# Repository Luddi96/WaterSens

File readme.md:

Universaler Zisternen-Füllstandsmesser

Einleitung:

Jeder Besitzer einer Regenzisterne kennt diese Frage: Wie viel Wasser verbleibt mir noch und wie viel hat der letzte Regen wieder aufgefüllt? Um Abhilfe zu schaffen gibt es eine Reihe an Messgeräten und Sensoren: Ganz simpel mit mehren Elektroden auf verschiedenen Höhen, kapazitiv unter Zuhilfenahme der Dielektrizitätskonstante des Wassers selbst, per Ultraschall oder per Druckmessung. Einige dieser Messungen haben Vorteile gegenüber anderen. In diesem Beitrag möchte ich Ihnen eine Methode zur Messung vorstellen, welche weder durch Temperatur, Luftdruck oder Leitfähigkeit des Wassers verfälscht wird und außerdem selbstreinigend (wartungsfrei) agiert. Die Messgenauigkeit liegt bei umgerechnet 20 Liter in einer 7500 Liter Zisterne, also etwa 0,3%!
Das Projekt involviert die Programmierung eines ATMega Mikrocontrollers, das Löten von SMD Bauteilen (es könnte aber auch als THT aufgebaut werden) sowie grundlegende mechanische Fähigkeiten.
Das Funktionsprinzip:
Wie funktioniert der Sensor? Im Prinzip ganz einfach: Man misst den Druck, den das Wasser an der tiefsten Stelle der Zisterne erzeugt. Dieser ist proportional zur Höhe des Wassers und somit (bei einer gleichförmigen Zisterne) ebenfalls proportional zum Füllstand. Würde man aber einfach einen Sensor auf den Grund der Zisterne herablassen, so stößt man auf 3 Probleme: 1. Solche Sensoren sind recht teuer (müssen ja auch wasserdicht sein) 2. Es gibt keine Möglichkeit, den Sensor periodisch zu nullen 3. Der Luftdruck beeinflusst das Ergebnis: 10hPa Druckunterschied bedeuten bereits 100mm Wassersäule oder einen Messfehler von etwa 750 Liter in bzw. 10% in einer 7500 Liter Zisterne.
Mit einem Trick können aber alle der eben genannten Einflüsse kompensiert werden: In die Zisterne wird lediglich ein dünner Schlauch mit einem Gewicht am offenen Ende eingeführt und bis zum Boden herabgelassen. In das andere Ende wird mit einer kleinen Luftpumpe so lange Luft gepumpt, bis dieser komplett gefüllt ist und erste Luftblasen austreten. Der Druck im Schlauch entspricht dann genau dem Druck am Boden der Zisterne. Mit einem empfindlichen Drucksensor kann dieser dann ausgelesen werden. Wenn der Schlauch vor und nach der Messung mittels einem Magnetventil entleert wird, können Umgebungsdruck und Langzeit-Drift des Drucksensor eliminiert werden. Ebenso ist das System durch das "Ausspülen" des Schlauches bei jeder Messung selbstreinigend.

Komponenten:

1x Miniatur-Luftpumpe JQB031 oder ähnlich https://bit.ly/2ENsoDM
2x 3-Wege Magnetventil DQF2-6A-4 von dyxminipump https://bit.ly/2G6OzFo
1x Schlauch-Verbinder-Sortiment https://bit.ly/31LYU29
1x 50cm Silikonschlauch (2mm ID) https://bit.ly/2QGRM0I
1x 5m Silikonschlauch (4mm ID) https://bit.ly/34PzMJN
1x MPRLS Sensor-Modul https://www.adafruit.com/product/3965
1x Funkmodul, z.B. NRF24L01
1x Hauptleiterplatte, BOM als ZIP im Anhang
1x LiPo Einzelzelle 1000mAh https://bit.ly/2EHX8WZ

Aufbau:

Die Ansteuerung der Pumpe und Magnetventile sowie das Auslesen und Auswerten des Drucksensor und das anschließende Versenden der Daten per Funk übernimmt die Hauptleiterplatte. Auf dieser befindet sich ein ATMega328P-AU, geflasht mit dem Arudino Nano Bootloader. Zur Ansteuerung der Aktoren genügt ein IRF7103. Da der Sensor mehrere Jahre ohne Batteriewechsel auskommen soll, wird zur Spannungsversorgung ein TPS7A05 LDO mit einer Ausgangsspannung von 3,3V und einem Eigenstromverbrauch von nur 1uA verbaut. Auch der Spannungsteiler zur Messung der Batteriespannung wird über einen Optokoppler geschalten. So kommt das Gesamtsystem auf 6uA Sleep-Strom und bis zu 2 Jahre Lebensdauer bei 2 Messungen am Tag.
Die Pumpe sowie Magnetventile werden wie folgt verbunden:

Mit dem ersten Magnetventil kann der Druck aus dem System abgelassen werden, das andere Magnetventil schneidet "Messschlauch" und Drucksensor vom Rest ab, um einen Druckabfall während der Messung zu verhindern.
Das ganze wird auf einem 3D-Druck-Träger (.stl in der zip-Datei enthalten) in ein Modulgehäuse wasserdicht eingebaut. Der Druckausgleich wird mit einem Druckausgleichselement erreicht.
In der Software sieht der Ablauf wie folgt aus:
Initialisierung: Ports, Variablen, etc. initialisieren, Sensorwert auf 0 setzen
Start einer Messung:
-Druck im offenen System 3x messen, Wert als "before" speichern
-Magnetventil 1 schließen, Pumpe aktivieren
-Nach bestimmter Zeit Magnetventil 2 schließen, Pumpe abschalten und Magnetventil 1 wieder öffnen (der Schlauch steht jetzt unter Druck)
-Druck 3x messen, Wert als "high" speichern
-Magnetventil 2 öffnen und Druck entweichen lassen
-Druck 3x messen und als "after" speichern
-Aus before, after und high die Druckdifferenz berechnen, das ist das Ergebnis.
Eine solche Messung dauert etwa 8 Sekunden.
Fazit und Ergebnisse:
Ich habe das System nun schon seit 2 Monaten in Betrieb. Um die Haltbarkeit zu testen habe ich den Messintervall auf 60 Sekunden verringert und insgesamt hat das System bereits über 25.000 Messungen durchgeführt - ohne Probleme. Die Standardabweichung der Messung liegt bei etwa 2,5mm Wassersäule oder 20 Liter bei einer 7500 Liter Zisterne. Mir gefällt das System sehr gut. Ich habe bereits ein weiteres System gebaut, welches bei einem Bekannten eingebaut wird. Dort ersetzen wir das Funkmodul durch ein LAN-Modul, das System wird zudem dauerhaft mit Strom versorgt.

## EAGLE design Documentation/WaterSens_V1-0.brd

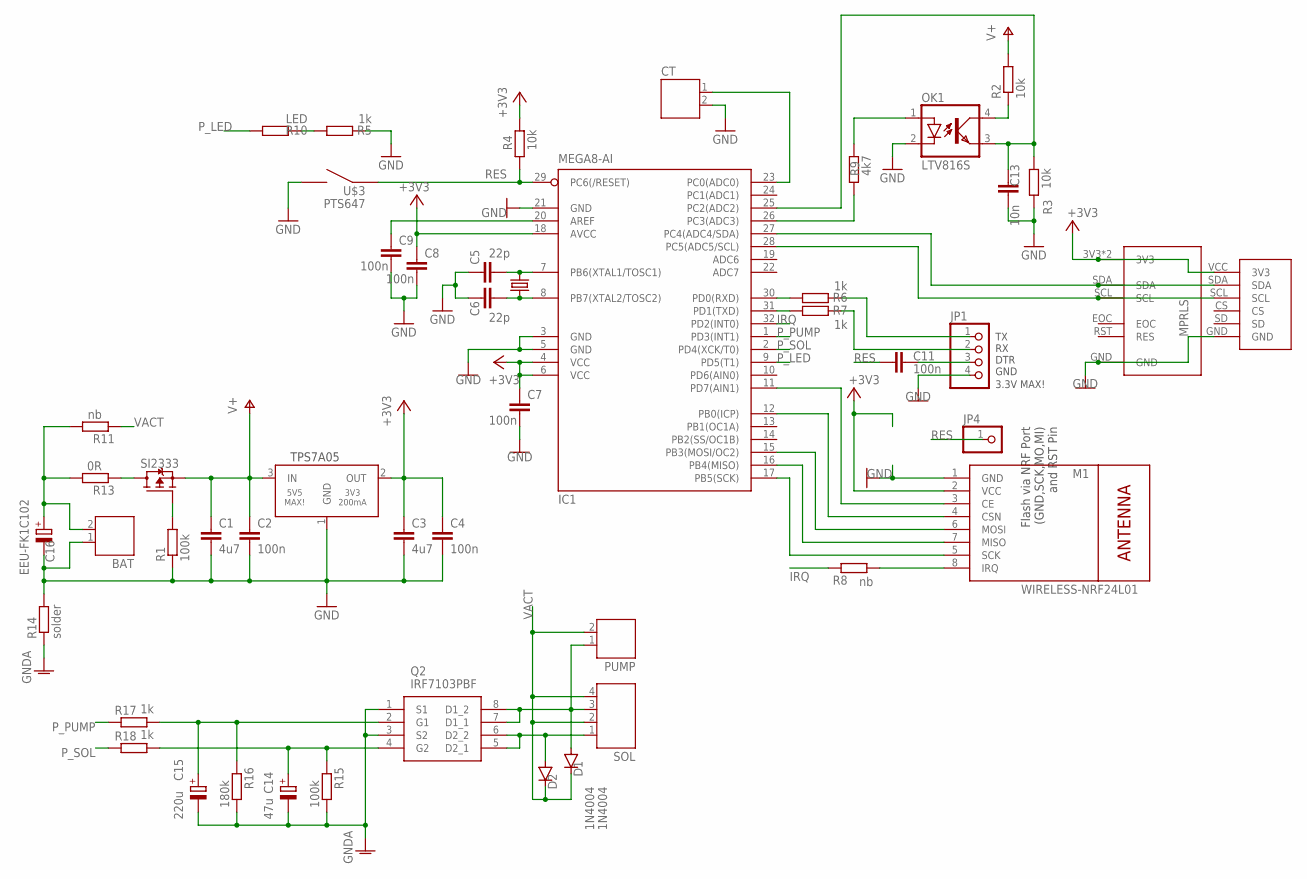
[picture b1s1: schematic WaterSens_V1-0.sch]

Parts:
BAT: JST-PH2
C1, C3: 4u7; C0805
C2, C4, C7, C8, C9, C11: 100n; C0805
C5, C6: 22p; C0805
C13: 10n; C0805
C14: 47u; E1,8-4
C15: 220u; E2,5-6E
C16: EEU-FK1C102; E5-10,5
CT: JST-PH2
D1, D2: 1N4004; DO41-10
IC1: MEGA8-AI; TQFP32-08
JP1: PINHD-1X4; 1X04
JP4: PINHD-1X1; 1X01
M1: WIRELESS-NRF24L01
OK1: LTV816S; DIL4-SMD
PUMP: JST-PH2
Q1: CRYSTALHC49UP; HC49UP
Q2: IRF7103PBF; SOIC127P600X175-8N
R1, R15: 100k; R0805
R2, R3, R4: 10k; R0805
R5, R6, R7, R17, R18: 1k; R0805
R8, R11: nb; R0805
R9: 4k7; R0805
R10: LED; R0805
R13: 0R; R0805
R14: solder; R0805
R16: 180k; R0805
SOL: JST-PH4
U$1: MPRLS_ADA
U$2: TEMP-HUM-PRES-BME280-3V3
U$3: PTS647
U$5: TPS7A05; SOT23
U$6: SI2333; SOT23

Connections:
+3V3: C3.1, C4.1, C7.1, C8.1, IC1.4 (VCC), IC1.6 (VCC), IC1.18 (AVCC), M1.2 (VCC), R4.2, U$1.3V3, U$1.VIN (3V3), U$2.VCC (3V3), U$5.2 (OUT)
GND: BAT.1, C1.2, C2.2, C3.2, C4.2, C5.1, C6.1, C7.2, C8.2, C9.2, C13.1, C16.-, CT.2, IC1.3 (GND), IC1.5 (GND), IC1.21 (GND), JP1.4, M1.1 (GND), OK1.2 (C), R1.1, R3.1, R5.1, R14.2, U$1.GND, U$2.GND, U$3.3, U$3.4, U$5.1 (GND)
GNDA: C14.-, C15.-, Q2.1 (S1), Q2.3 (S2), R14.1, R15.2, R16.2
IRQ: IC1.32 (PD2(INT0)), R8.2
unnamed: IC1.27 (PC4(ADC4/SDA)), U$1.SDA, U$2.SDA
unnamed: IC1.28 (PC5(ADC5/SCL)), U$1.SCL, U$2.SCL
unnamed: BAT.2, C16.+, R11.2, R13.2
unnamed: C5.2, IC1.7 (PB6(XTAL1/TOSC1)), Q1.2
unnamed: R1.2, U$6.1 (G)
unnamed: OK1.4 (COL), R2.1
unnamed: C14.+, Q2.4 (G2), R15.1, R18.2
unnamed: C15.+, Q2.2 (G1), R16.1, R17.2
unnamed: IC1.26 (PC3(ADC3)), R9.1
unnamed: C6.2, IC1.8 (PB7(XTAL2/TOSC2)), Q1.1
unnamed: IC1.11 (PD7(AIN1)), M1.3 (CE)
unnamed: IC1.30 (PD0(RXD)), R6.2
unnamed: C9.1, IC1.20 (AREF)
unnamed: OK1.1 (A), R9.2
unnamed: IC1.31 (PD1(TXD)), R7.2
unnamed: JP1.1, R6.1
unnamed: JP1.2, R7.1
unnamed: C11.2, JP1.3
unnamed: IC1.12 (PB0(ICP)), M1.4 (CSN)
unnamed: IC1.15 (PB3(MOSI/OC2)), M1.6 (MOSI)
unnamed: IC1.16 (PB4(MISO)), M1.7 (MISO)
unnamed: IC1.17 (PB5(SCK)), M1.5 (SCK)
unnamed: M1.8 (IRQ), R8.1
unnamed: R5.2, R10.1
unnamed: R13.1, U$6.3 (D)
unnamed: D1.A, PUMP.1, Q2.7 (D1_1), Q2.8 (D1_2), SOL.3
unnamed: D2.A, Q2.5 (D2_1), Q2.6 (D2_2), SOL.1
unnamed: CT.1, IC1.23 (PC0(ADC0))
P_LED: IC1.9 (PD5(T1)), R10.2
P_PUMP: IC1.1 (PD3(INT1)), R17.1
P_SOL: IC1.2 (PD4(XCK/T0)), R18.1
RES: C11.1, IC1.29 (PC6(/RESET)), JP4.1, R4.1, U$3.1, U$3.2
U_MESS: C13.2, IC1.25 (PC2(ADC2)), OK1.3 (EMIT), R3.2
V+: C1.1, C2.1, R2.2, U$5.3 (IN), U$6.2 (S)
VACT: D1.C, D2.C, PUMP.2, R11.1, SOL.2, SOL.4

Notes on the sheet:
TX RX DTR GND
3.3V MAX!
TPS7A05
Flash via NRF Port (GND,SCK,MO,MI) and RST Pin

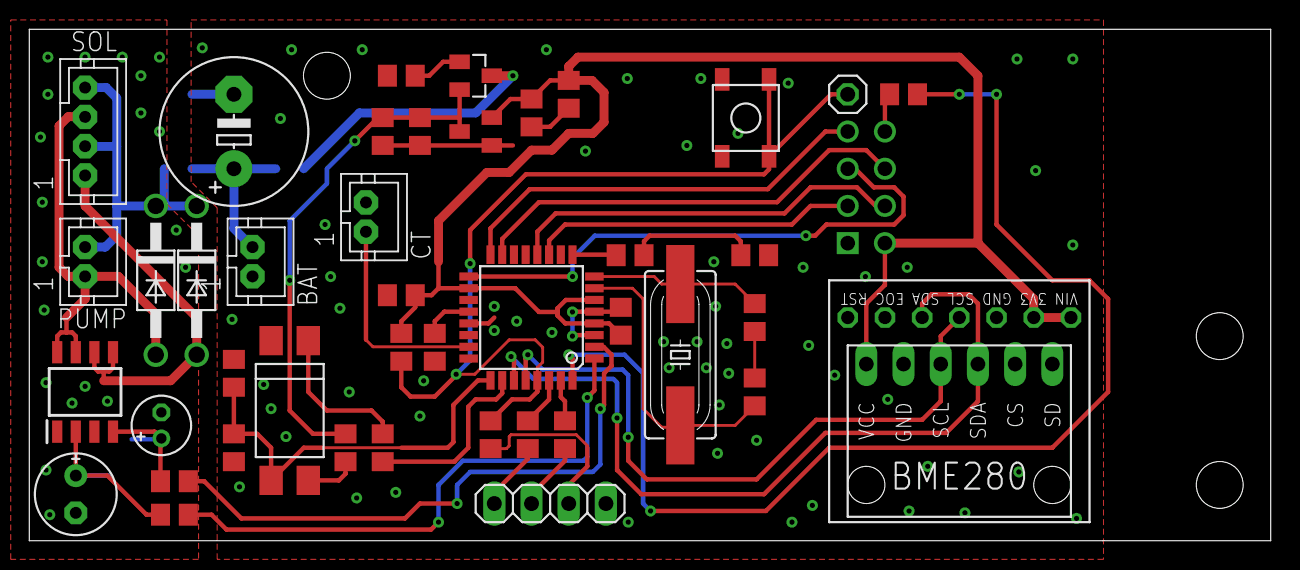
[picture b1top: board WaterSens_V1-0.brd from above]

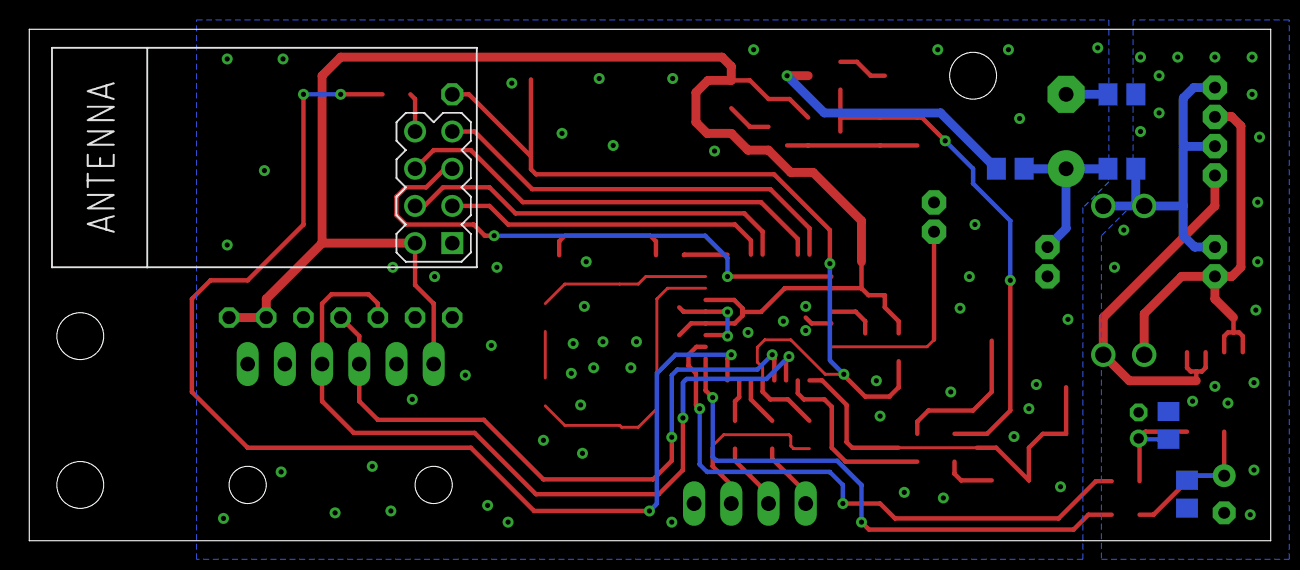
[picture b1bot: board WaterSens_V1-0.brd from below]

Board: 2 copper layers, 84.8 x 34.9 mm, 49 parts (6 on the bottom side), 39 nets.

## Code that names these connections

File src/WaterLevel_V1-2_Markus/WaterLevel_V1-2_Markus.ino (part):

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#define P_UBAT_EN A3 //This pin enables UBAT measurement (approx. 200uA)
#define P_UBAT_MEAS A2 //Analog pin to read UBAT via divider
#define P_LED_USER 5 //Led for button illumination (approx. 20mA)
#define P_SOL 4 //Solenoid enable (approx. 400mA)
#define P_PUMP 3 //Pump enable (approx. 600mA)

#define T20TO6 1
#define T6TO13 2
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  pinMode(P_UBAT_EN, OUTPUT);
  pinMode(P_LED_USER, OUTPUT);

  pinMode(P_SOL, OUTPUT);
  digitalWrite(P_SOL, LOW);
  
  pinMode(P_PUMP, OUTPUT);
  digitalWrite(P_PUMP, LOW);
}

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    
  }
  
  float res = 0;
  for(int i = 0; i < cnt; i++)
  {
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
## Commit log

2021-03-17 initial
2021-03-17 Images added
2021-03-17 Images renewed

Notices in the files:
parts and their libraries:
diy-modules: Released under the Creative Commons Attribution 4.0 International License: http://creativecommons.org/licenses/by/4.0
